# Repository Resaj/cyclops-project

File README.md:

# Cyclops-project

Robot siguelíneas Open Source, diseñado para introducir a nuevos constructores en la robótica de competición. Se compone de dos PCBs: la del chasis autosoportado con la electrónica principal; y la de sensores, que es intercambiable para poder adaptarlo a diferentes pruebas de seguimiento de línea. Incorpora extras de sensores de distancia, cámara y bluetooth, para poder participar en otras pruebas como carreras y laberinto, además de experimentar nuevos métodos de seguimiento de línea o degradado.

El chasis del robot incorpora:
- Arduino nano
- Batería Lipo 2S
- Pulsadores de selección de menú
- Leds indicadores
- Driver de motores TB6612FNG
- Micromotores 10:1 HP 6V con reductora metálica y encoders en cuadratura
- Ruedas de 32mm de diámetro
- Sensor frontal de distancia de 80cm para detección de oponentes (necesario para carreras)
- Sensores laterales de distancia de 35cm para detección de oponentes (necesario para carreras)
- Cámara de 1x128 píxeles para seguimiento de línea y detección de oponentes
- Expansor I2C para poder soportar todos los periféricos incorporados

La PCB de sensores es intercambiable e incorpora:
- Sensores CNY70 para seguimiento de línea (6 para velocista; 8 para rastreador)
- Multiplexor para los sensores de línea

## Manuales y guías del proyecto

Disponibles en la carpeta [manuals](https://github.com/Resaj/cyclops-project/tree/master/manuals):
- [Tutorial 1](https://github.com/Resaj/cyclops-project/blob/master/manuals/Tutorial%201%20-%20Bater%C3%ADas%20Lipo.pdf) - Baterías Lipo
- [Tutorial 2](https://github.com/Resaj/cyclops-project/blob/master/manuals/Tutorial%202%20-%20Impresi%C3%B3n%20de%20las%20piezas%20del%20robot.pdf) - Impresión de las piezas del robot
- [Tutorial 3](https://github.com/Resaj/cyclops-project/blob/master/manuals/Tutorial%203%20-%20Montaje%20del%20robot.pdf) - Montaje del robot
- [Tutorial 4](https://github.com/Resaj/cyclops-project/blob/master/manuals/Tutorial%204%20-%20Configuraci%C3%B3n%20del%20bluetooth%20HC-05.pdf) - Configuración del Bluetooth HC-05
- [Tutorial 5](https://github.com/Resaj/cyclops-project/blob/master/manuals/Tutorial%205%20-%20Primeras%20pruebas.pdf) - Primeras pruebas

A medida que el proyecto vaya avanzando se añadirán más tutoriales para completar la información y facilitar el montaje y la programación del robot.

## Retos planteados para el usuario

Cyclops es un proyecto base para cualquier persona que quiera adentrarse en el mundo de la robótica a través de las competiciones. Por un lado se proporciona una base para el aprendizaje y para facilitar la participación; por otro, se plantean una serie de retos e ideas que servirán a los usuarios para afrontar el desarrollo de un proyecto de robótica y profundizar experimentando con las mejoras:

* General:
  * Mejoras de comunicación por bluetooth con logs de telemetría
*  Rastreador:
  * [Reconocimiento de marcas de giro y selección del camino correcto en las bifurcaciones](https://www.youtube.com/watch?v=3Fi3WpjZuA0)
* Velocistas:
  * Reconocimiento de la [pista](https://github.com/Resaj/basic-circuit-maker) con encoders para acelerar en las rectas y frenar antes de las curvas
  * Adaptación del PID de seguimiento de línea para competir sobre [pistas de degradado](https://github.com/Resaj/circuit-maker)
* Carreras:
  * Detección de oponentes con los sensores de distancia para cambiar de carril y efectuar adelantamientos
  * Implementación de un PID para seguir a un oponente en carreras cuando no se pueda cambiar de carril para adelantar
  * Reconocimiento y seguimiento de líneas y degradados con cámara
* Laberinto:
  * Adaptación del algoritmo de laberinto para seguir la pared derecha en vez de la izquierda
  * Guiarse con los dos sensores laterales y con los encoders para ir siempre centrado en las casillas del laberinto
  * Memorizar las casillas del laberinto en el primer intento para que el robot sea capaz de resolverlo al segundo intento tomando el camino más corto

## Preguntas frecuentes

Puedes encontrar un listado de las preguntas frecuentes con sus respectivas respuestas en la [wiki del proyecto](https://github.com/Resaj/cyclops-project/wiki/FAQ).

## Autor

[Rubén Espino San José](https://github.com/Resaj)

## Agradecimientos y aportaciones

- A Alex @TCRobotics de BricoLabs, por su [tutorial para adaptar el driver CH340G de la Arduino Nano para MAC OS](https://bricolabs.cc/wiki/guias/mac_os_y_ch340)
- A [José Luis Villarejo](https://github.com/movilujo), por los [diseños de las PCBs de Cyclops en FreeCAD](https://github.com/Resaj/cyclops-project/tree/master/hw/FreeCAD/PCBs)
- A [Juan Alberto Babío](https://github.com/jbabio), por la adaptación del [soporte regulable para la cámara](https://github.com/Resaj/cyclops-project/blob/master/hw/FreeCAD/Soporte_inclinable_camara_Aliexpress.stl)
- A Óscar de BricoGeek, por sus streaming ([1](https://www.youtube.com/watch?v=NNreAwnH6MY) y [2](https://www.youtube.com/watch?v=S61M1Ss7pH4)) del montaje de Cyclops-Project
- A [Álex](https://github.com/robotaleh) y [Manuel](https://github.com/20leunam), de [OPRobots](https://github.com/OPRobots), por su [App para calibrar y controlar el robot mediante el bluetooth del móvil](https://github.com/Resaj/cyclops-project/tree/master/fw/PID_seguimiento_linea/PID_seguimiento_linea_PIDfromBT)
- A [Javier Martín](https://github.com/jamarju), por su [adaptación del bootloader de la Arduino para la carga de programas por bluetooth](https://github.com/jamarju/hexloader-avr)

## Licencia

Todos estos productos están liberados mediante [Creative Commons Attribution-ShareAlike 4.0 International License](http://creativecommons.org/licenses/by-sa/4.0/).

_All these products are released under [Creative Commons Attribution-ShareAlike 4.0 International License](http://creativecommons.org/licenses/by-sa/4.0/)._

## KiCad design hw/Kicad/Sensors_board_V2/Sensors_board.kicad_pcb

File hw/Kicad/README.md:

Las huellas de componentes empleadas en el diseño e incluídas en las subcarpetas .pretty pertenecen al repositorio [kicad-footprints](https://github.com/KiCad/kicad-footprints).
Igualmente, los ficheros 3D empleados en el diseño e incluidos en las subcarpetas .3dshapes pertenecen al repositorio [kicad-packages3D](https://github.com/KiCad/kicad-packages3D).

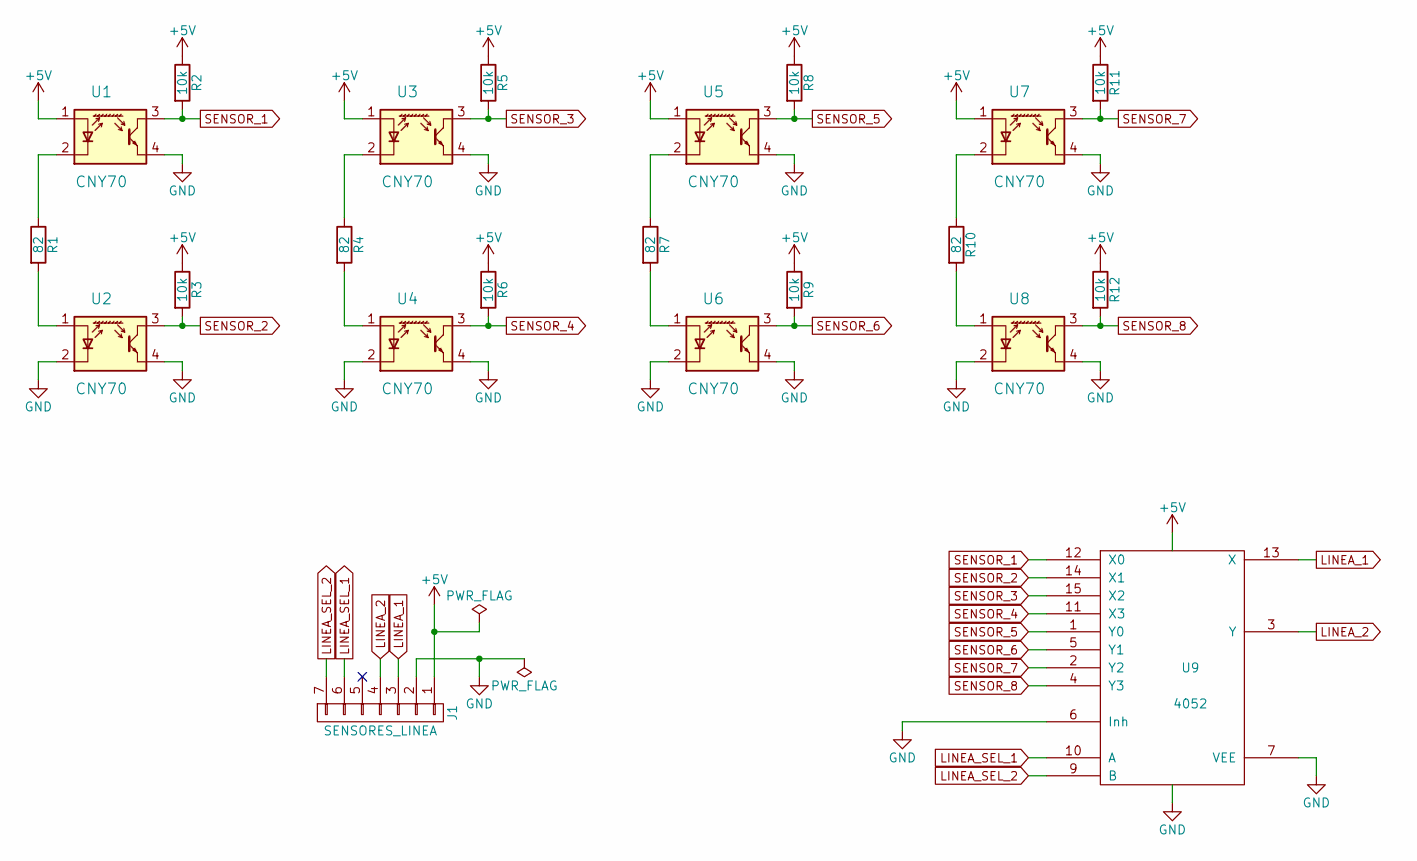
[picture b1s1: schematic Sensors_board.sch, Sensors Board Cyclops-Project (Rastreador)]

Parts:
J1: SENSORES_LINEA; PinHeader_1x07_P2.54mm_Horizontal
R1, R4, R7, R10: 82; R_Axial_DIN0207_L6.3mm_D2.5mm_P10.16mm_Horizontal
R2, R3, R5, R6, R8, R9, R11, R12: 10k; R_Axial_DIN0207_L6.3mm_D2.5mm_P10.16mm_Horizontal
U1, U2, U3, U4, U5, U6, U7, U8: CNY70; Vishay_CNY70
U9: 4052; DIP-16_W7.62mm_Socket_LongPads

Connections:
+5V: J1.1, R2.1, R3.1, R5.1, R6.1, R8.1, R9.1, R11.1, R12.1, U1.1 (A), U3.1 (A), U5.1 (A), U7.1 (A), U9.16 (VDD)
GND: J1.2, U1.4 (E), U2.2 (K), U2.4 (E), U3.4 (E), U4.2 (K), U4.4 (E), U5.4 (E), U6.2 (K), U6.4 (E), U7.4 (E), U8.2 (K), U8.4 (E), U9.6 (Inh), U9.7 (VEE), U9.8 (VSS)
LINEA_1: J1.3, U9.13 (X)
LINEA_2: J1.4, U9.3 (Y)
LINEA_SEL_1: J1.6, U9.10 (A)
LINEA_SEL_2: J1.7, U9.9 (B)
unnamed: R1.1, U1.2 (K)
unnamed: R1.2, U2.1 (A)
unnamed: R4.1, U3.2 (K)
unnamed: R4.2, U4.1 (A)
unnamed: R7.1, U5.2 (K)
unnamed: R7.2, U6.1 (A)
unnamed: R10.1, U7.2 (K)
unnamed: R10.2, U8.1 (A)
SENSOR_1: R2.2, U1.3 (C), U9.12 (X0)
SENSOR_2: R3.2, U2.3 (C), U9.14 (X1)
SENSOR_3: R5.2, U3.3 (C), U9.15 (X2)
SENSOR_4: R6.2, U4.3 (C), U9.11 (X3)
SENSOR_5: R8.2, U5.3 (C), U9.1 (Y0)
SENSOR_6: R9.2, U6.3 (C), U9.5 (Y1)
SENSOR_7: R11.2, U7.3 (C), U9.2 (Y2)
SENSOR_8: R12.2, U8.3 (C), U9.4 (Y3)

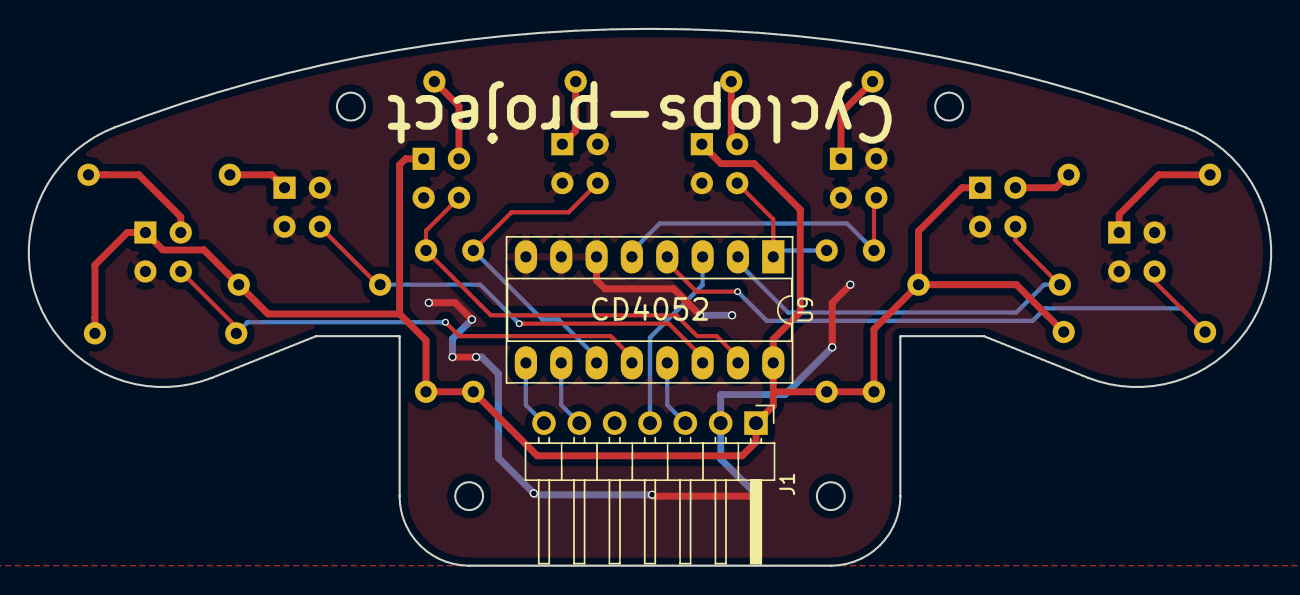
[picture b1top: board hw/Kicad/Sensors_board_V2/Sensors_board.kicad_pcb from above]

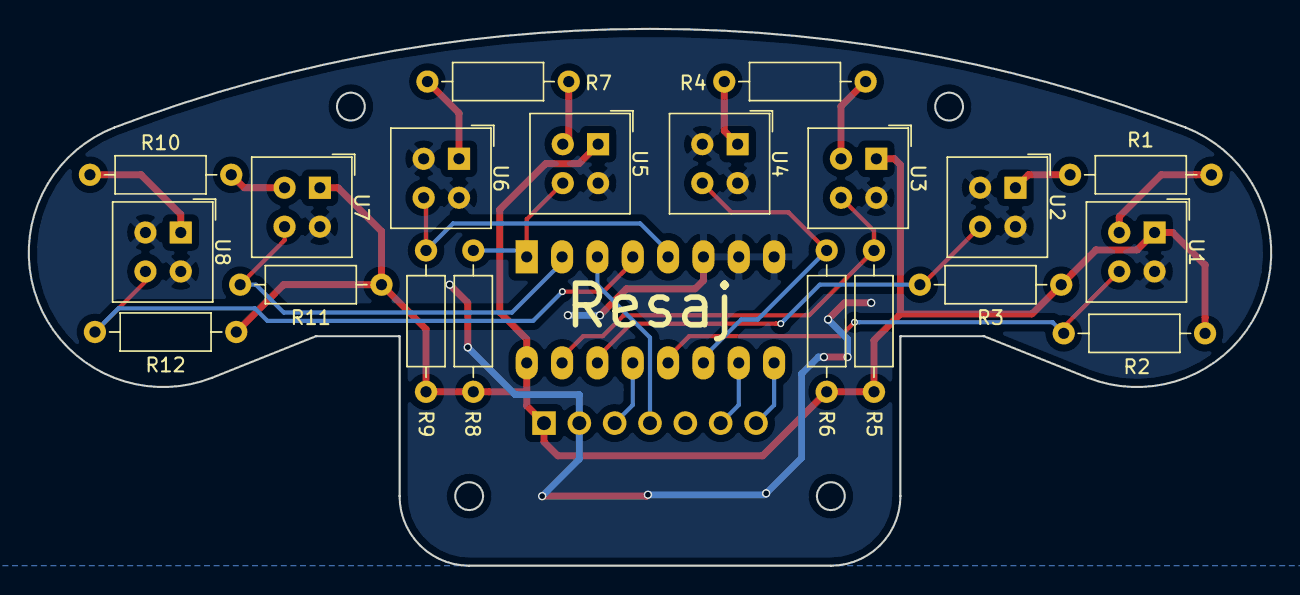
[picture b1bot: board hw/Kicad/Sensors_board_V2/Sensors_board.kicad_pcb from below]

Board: 2 copper layers, 89.3 x 38.6 mm, 22 parts (20 on the bottom side), 22 nets.

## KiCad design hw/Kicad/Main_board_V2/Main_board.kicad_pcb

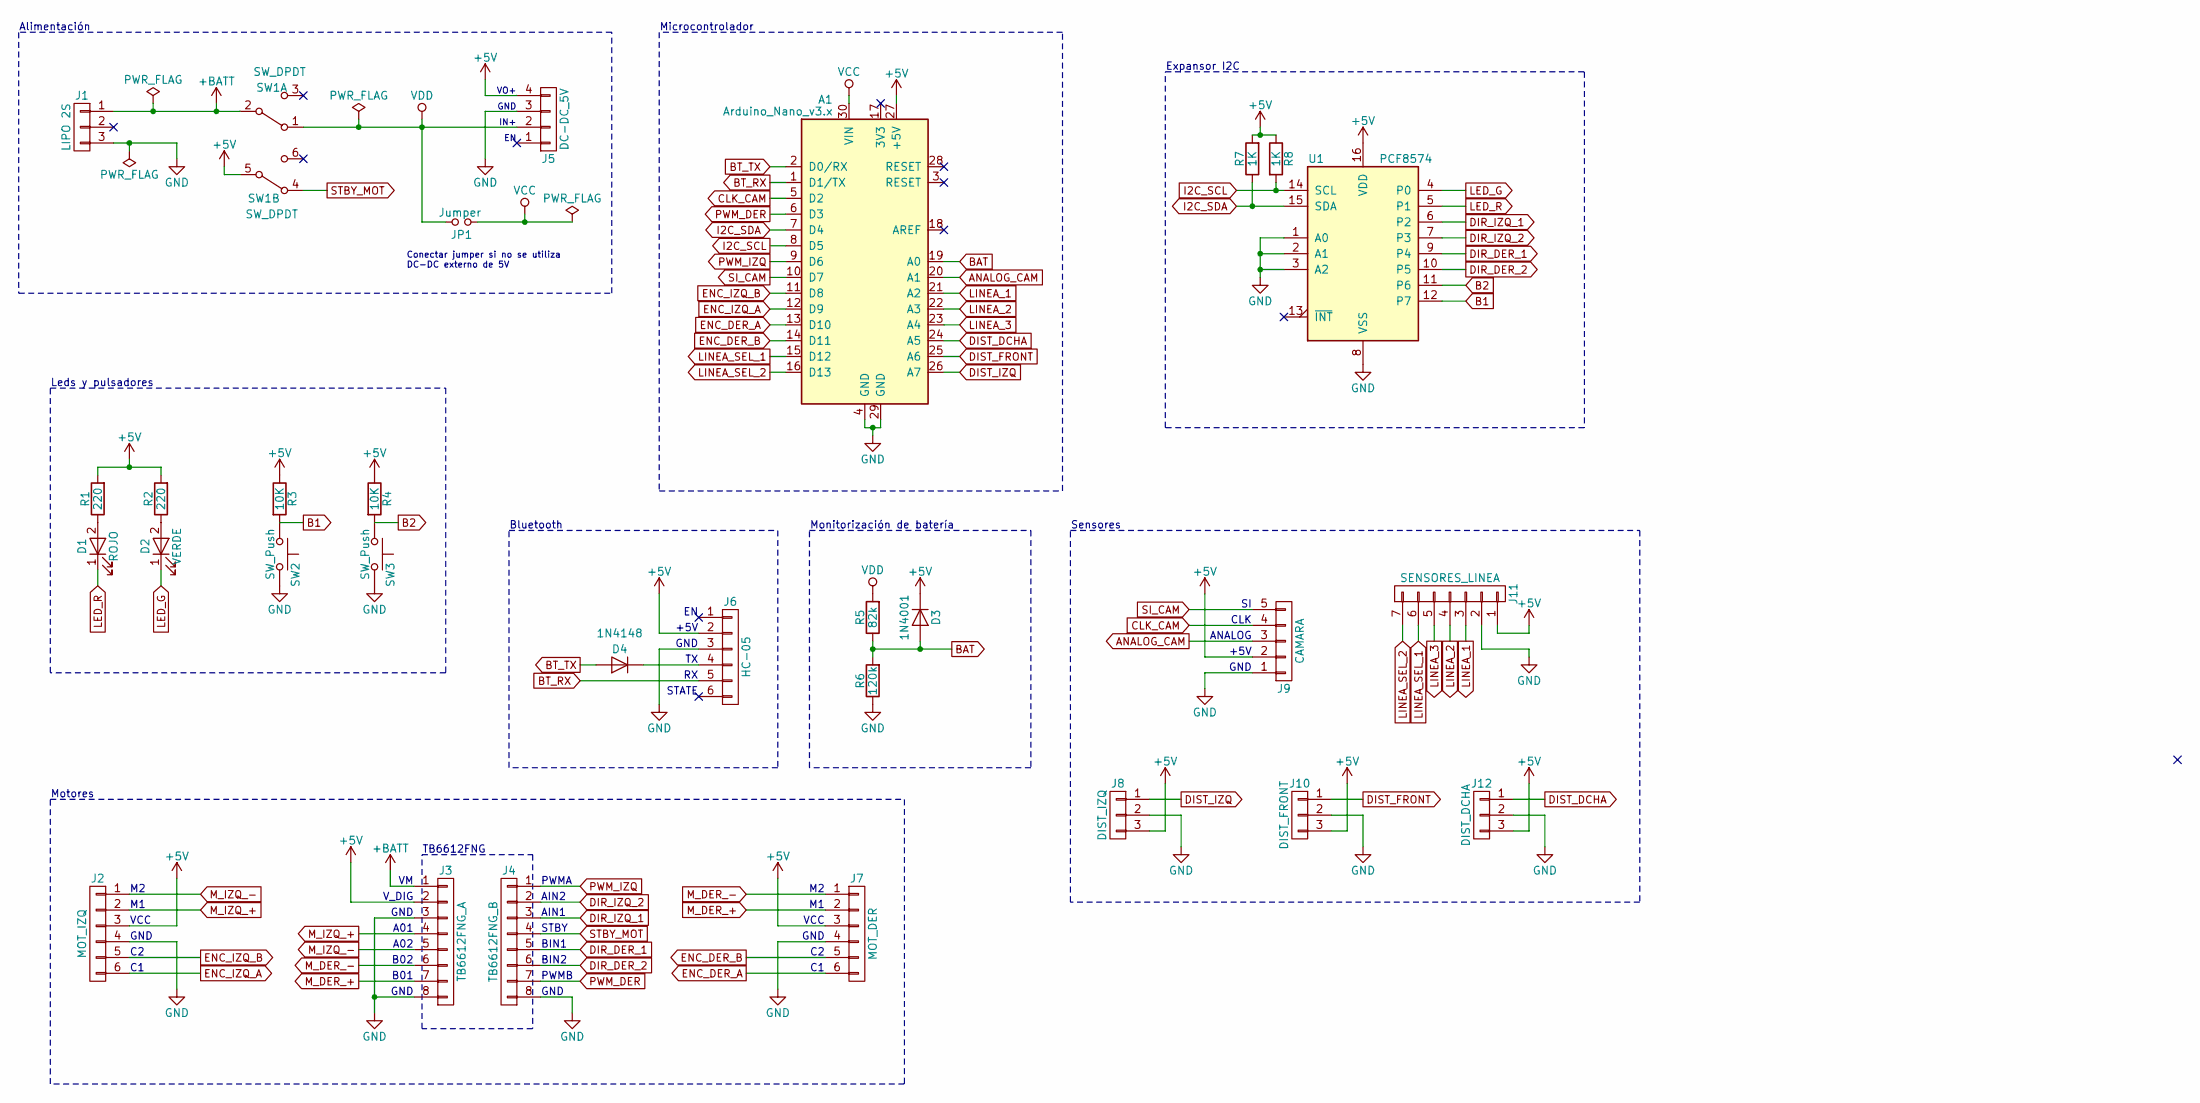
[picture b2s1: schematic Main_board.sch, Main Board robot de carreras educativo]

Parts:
A1: Arduino_Nano_v3.x; Arduino_Nano
D1: ROJO; LED_D3.0mm
D2: VERDE; LED_D3.0mm
D3: 1N4001; D_A-405_P10.16mm_Horizontal
D4: 1N4148; D_A-405_P10.16mm_Horizontal
J1: LIPO 2S; JST_XH_B03B-XH-A_1x03_P2.50mm_Vertical
J2: MOT_IZQ; PinHeader_1x06_P2.00mm_Vertical
J3: TB6612FNG_A; PinSocket_1x08_P2.54mm_Vertical
J4: TB6612FNG_B; PinSocket_1x08_P2.54mm_Vertical
J5: DC-DC_5V; PinSocket_1x04_P2.54mm_Horizontal
J6: HC-05; PinSocket_1x06_P2.54mm_Vertical
J7: MOT_DER; PinHeader_1x06_P2.00mm_Vertical
J8: DIST_IZQ; PinHeader_1x03_P2.00mm_Vertical
J9: CAMARA; PinHeader_1x05_P2.54mm_Vertical
J10: DIST_FRONT; PinHeader_1x03_P2.00mm_Vertical
J11: SENSORES_LINEA; PinSocket_1x07_P2.54mm_Horizontal
J12: DIST_DCHA; PinHeader_1x03_P2.00mm_Vertical
JP1: Jumper; SolderJumper-2_P1.3mm_Open_Pad1.0x1.5mm
R1, R2: 220; R_Axial_DIN0207_L6.3mm_D2.5mm_P10.16mm_Horizontal
R3, R4: 10K; R_Axial_DIN0207_L6.3mm_D2.5mm_P10.16mm_Horizontal
R5: 82k; R_Axial_DIN0207_L6.3mm_D2.5mm_P10.16mm_Horizontal
R6: 120k; R_Axial_DIN0207_L6.3mm_D2.5mm_P10.16mm_Horizontal
R7, R8: 1K; R_Axial_DIN0207_L6.3mm_D2.5mm_P10.16mm_Horizontal
SW1: SW_DPDT; SW_CuK_JS202011CQN_DPDT_Straight
SW2, SW3: SW_Push; SW_PUSH_6mm
U1: PCF8574; DIP-16_W7.62mm_Socket_LongPads

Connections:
+5V: A1.27 (+5V), D3.1 (K), J2.3, J3.2, J5.4, J6.2, J7.3, J8.3, J9.2, J10.3, J11.1, J12.3, R1.2, R2.2, R3.1, R4.1, R7.2, R8.1, SW1.5 (B), U1.16 (VDD)
+BATT: J1.1, J3.1, SW1.2 (B)
ANALOG_CAM: A1.20 (A1), J9.3
B1: R3.2, SW2.1, U1.12 (P7)
B2: R4.2, SW3.1, U1.11 (P6)
BAT: A1.19 (A0), D3.2 (A), R5.1, R6.2
BT_RX: A1.1 (D1/TX), J6.5
BT_TX: A1.2 (D0/RX), D4.2 (A)
CLK_CAM: A1.5 (D2), J9.4
DIR_DER_1: J4.5, U1.9 (P4)
DIR_DER_2: J4.6, U1.10 (P5)
DIR_IZQ_1: J4.3, U1.6 (P2)
DIR_IZQ_2: J4.2, U1.7 (P3)
DIST_DCHA: A1.24 (A5), J12.1
DIST_FRONT: A1.25 (A6), J10.1
DIST_IZQ: A1.26 (A7), J8.1
ENC_DER_A: A1.13 (D10), J7.6
ENC_DER_B: A1.14 (D11), J7.5
ENC_IZQ_A: A1.12 (D9), J2.6
ENC_IZQ_B: A1.11 (D8), J2.5
GND: A1.4 (GND), A1.29 (GND), J1.3, J2.4, J3.3, J3.8, J4.8, J5.3, J6.3, J7.4, J8.2, J9.1, J10.2, J11.2, J12.2, R6.1, SW2.2, SW3.2, U1.1 (A0), U1.2 (A1), U1.3 (A2), U1.8 (VSS)
I2C_SCL: A1.8 (D5), R8.2, U1.14 (SCL)
I2C_SDA: A1.7 (D4), R7.1, U1.15 (SDA)
LED_G: D2.1 (K), U1.4 (P0)
LED_R: D1.1 (K), U1.5 (P1)
LINEA_1: A1.21 (A2), J11.3
LINEA_2: A1.22 (A3), J11.4
LINEA_3: A1.23 (A4), J11.5
LINEA_SEL_1: A1.15 (D12), J11.6
LINEA_SEL_2: A1.16 (D13), J11.7
M_DER_+: J3.7, J7.2
M_DER_-: J3.6, J7.1
M_IZQ_+: J2.2, J3.4
M_IZQ_-: J2.1, J3.5
unnamed: D1.2 (A), R1.1
unnamed: D2.2 (A), R2.1
unnamed: D4.1 (K), J6.4
PWM_DER: A1.6 (D3), J4.7
PWM_IZQ: A1.9 (D6), J4.1
SI_CAM: A1.10 (D7), J9.5
STBY_MOT: J4.4, SW1.4 (A)
VCC: A1.30 (VIN), JP1.1
VDD: J5.2, JP1.2, R5.2, SW1.1 (A)

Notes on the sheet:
VO+
IN+
GND
Conectar jumper si no se utiliza DC-DC externo de 5V
Alimentación
Microcontrolador
Leds y pulsadores
Monitorización de batería
V_DIG
A01
A02
B02
B01
PWMB
PWMA
AIN2
AIN1
STBY
BIN1
BIN2
VCC
TB6612FNG
Motores
+5V
STATE
Bluetooth
ANALOG
CLK
Sensores
Expansor I2C

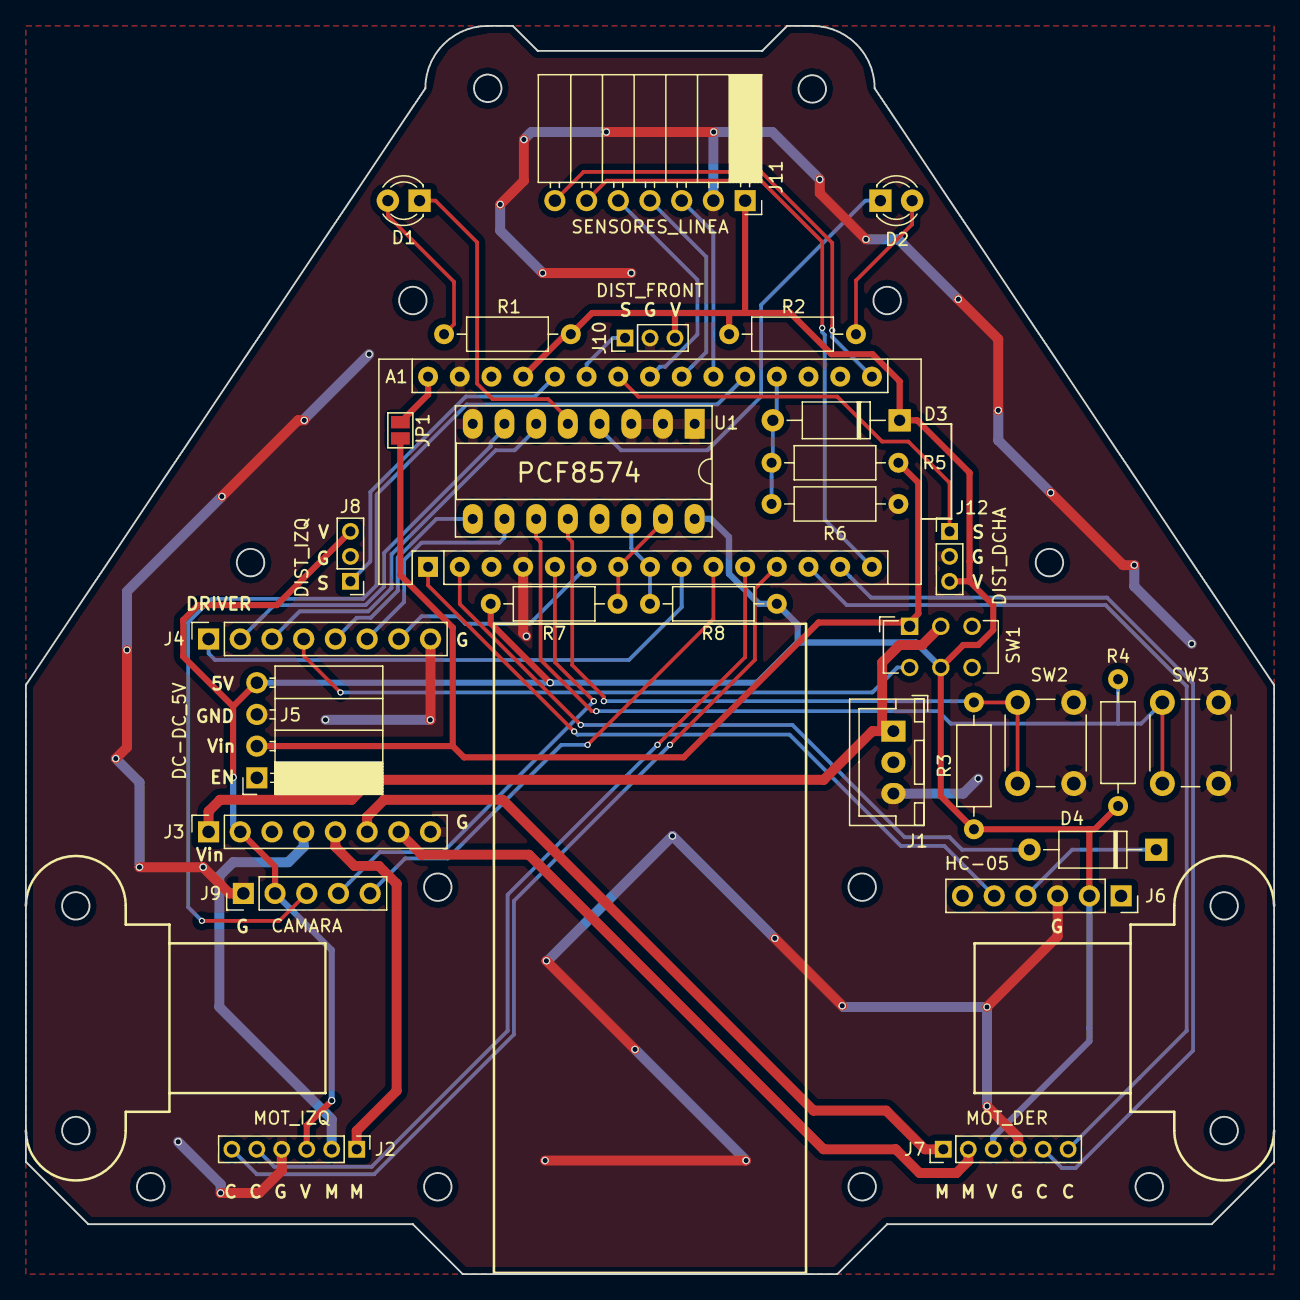
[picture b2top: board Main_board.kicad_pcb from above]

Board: 2 copper layers, 100.0 x 100.0 mm, 30 parts (0 on the bottom side), 43 nets.

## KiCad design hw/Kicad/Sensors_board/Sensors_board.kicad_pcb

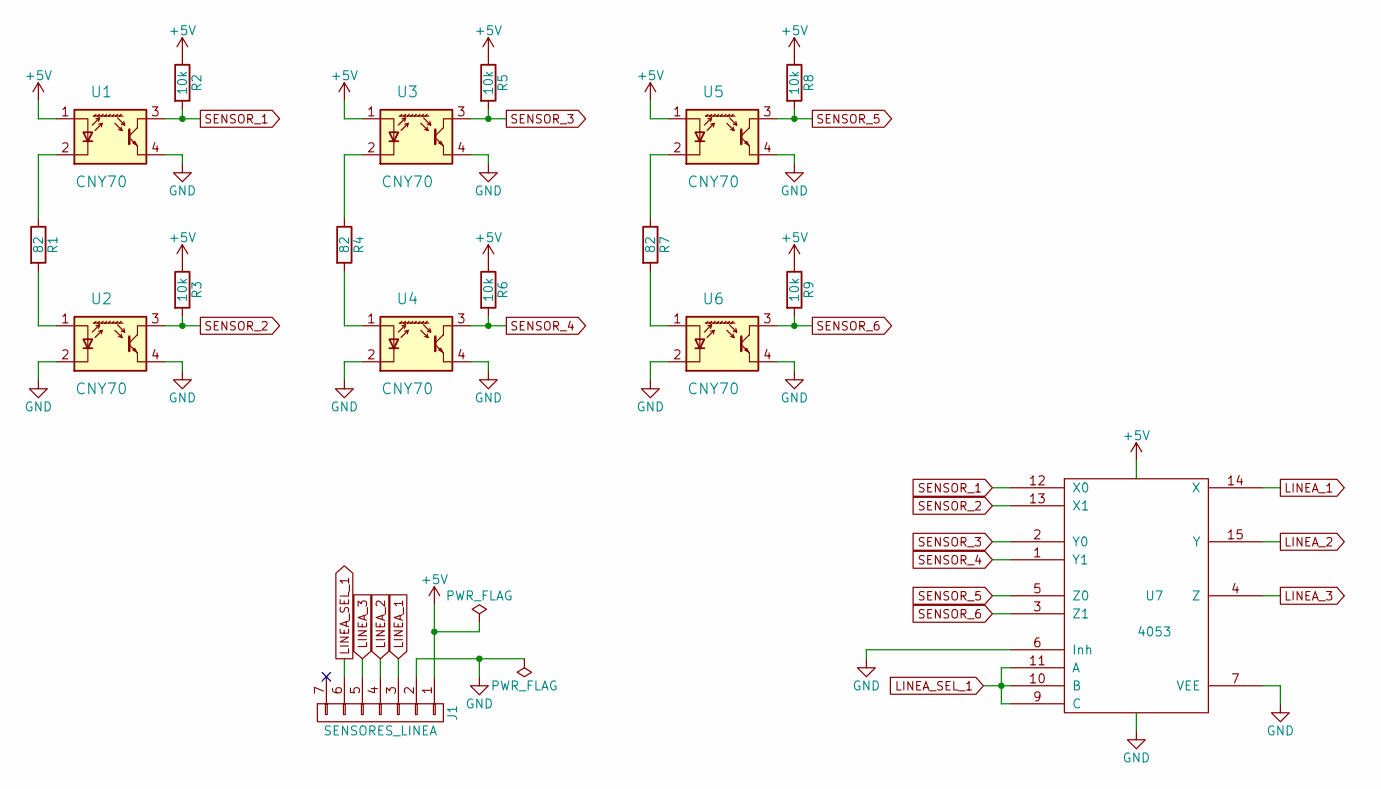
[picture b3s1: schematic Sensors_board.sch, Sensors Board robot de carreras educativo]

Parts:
J1: SENSORES_LINEA; PinHeader_1x07_P2.54mm_Horizontal
R1, R4, R7: 82; R_Axial_DIN0207_L6.3mm_D2.5mm_P10.16mm_Horizontal
R2, R3, R5, R6, R8, R9: 10k; R_Axial_DIN0207_L6.3mm_D2.5mm_P10.16mm_Horizontal
U1, U2, U3, U4, U5, U6: CNY70; Vishay_CNY70
U7: 4053; DIP-16_W7.62mm_Socket_LongPads

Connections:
+5V: J1.1, R2.1, R3.1, R5.1, R6.1, R8.1, R9.1, U1.1 (A), U3.1 (A), U5.1 (A), U7.16 (VDD)
GND: J1.2, U1.4 (E), U2.2 (K), U2.4 (E), U3.4 (E), U4.2 (K), U4.4 (E), U5.4 (E), U6.2 (K), U6.4 (E), U7.6 (Inh), U7.7 (VEE), U7.8 (VSS)
LINEA_1: J1.3, U7.14 (X)
LINEA_2: J1.4, U7.15 (Y)
LINEA_3: J1.5, U7.4 (Z)
LINEA_SEL_1: J1.6, U7.9 (C), U7.10 (B), U7.11 (A)
unnamed: R1.1, U1.2 (K)
unnamed: R1.2, U2.1 (A)
unnamed: R4.1, U3.2 (K)
unnamed: R4.2, U4.1 (A)
unnamed: R7.1, U5.2 (K)
unnamed: R7.2, U6.1 (A)
SENSOR_1: R2.2, U1.3 (C), U7.12 (X0)
SENSOR_2: R3.2, U2.3 (C), U7.13 (X1)
SENSOR_3: R5.2, U3.3 (C), U7.2 (Y0)
SENSOR_4: R6.2, U4.3 (C), U7.1 (Y1)
SENSOR_5: R8.2, U5.3 (C), U7.5 (Z0)
SENSOR_6: R9.2, U6.3 (C), U7.3 (Z1)

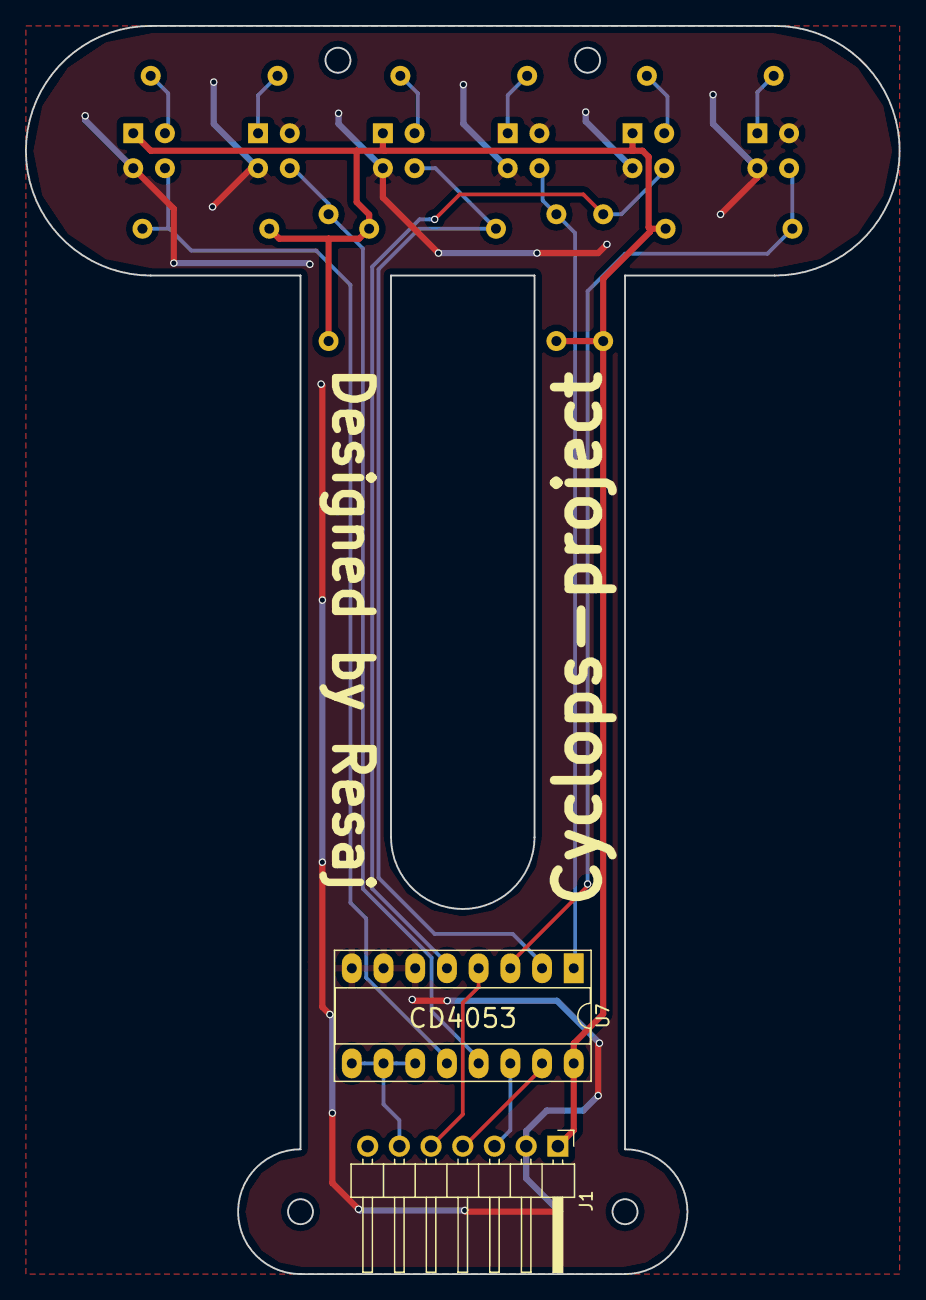
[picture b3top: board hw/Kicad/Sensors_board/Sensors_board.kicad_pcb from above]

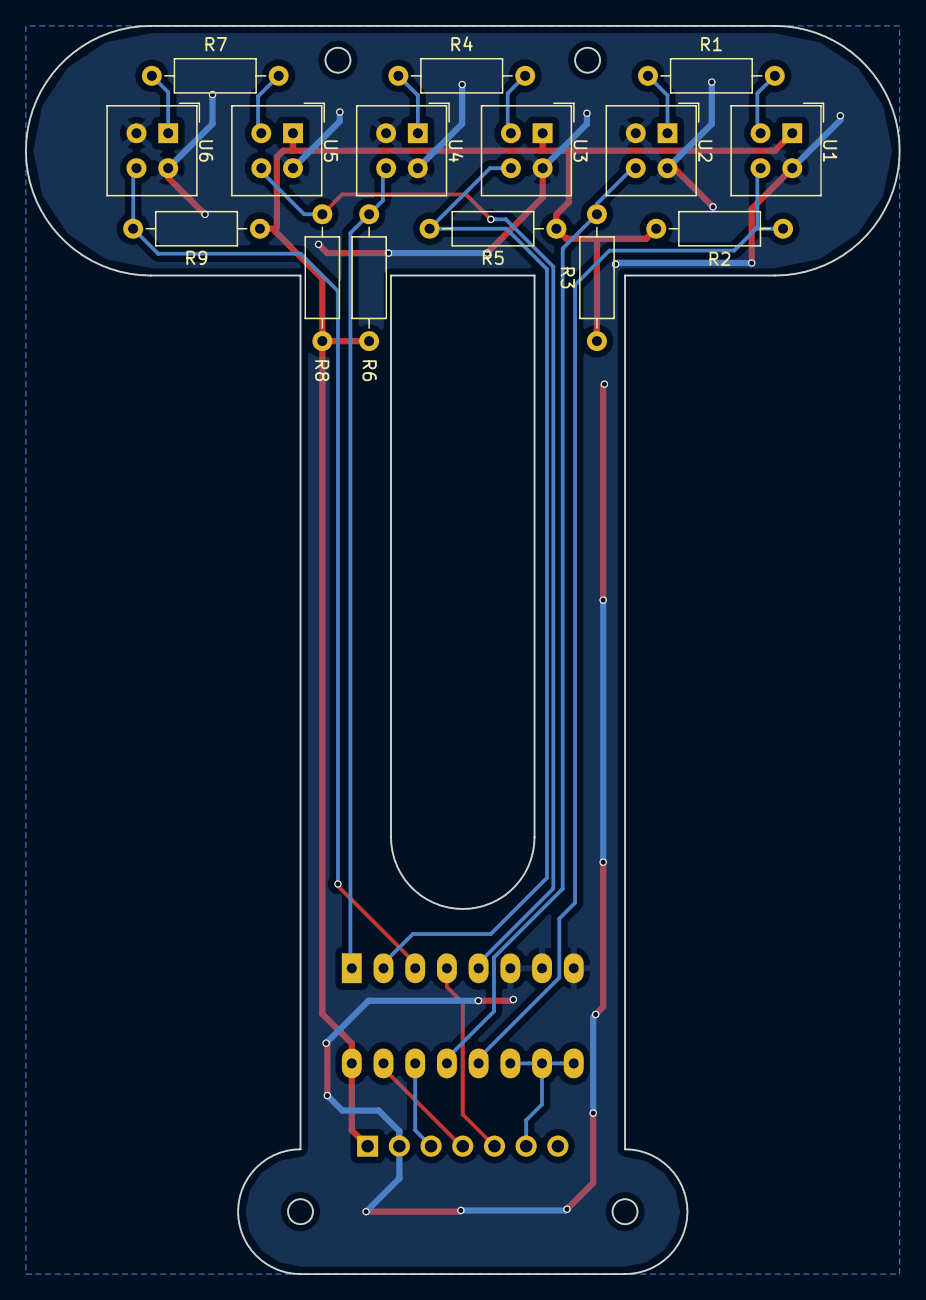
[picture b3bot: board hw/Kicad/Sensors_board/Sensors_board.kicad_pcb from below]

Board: 2 copper layers, 70.0 x 100.0 mm, 17 parts (15 on the bottom side), 18 nets.

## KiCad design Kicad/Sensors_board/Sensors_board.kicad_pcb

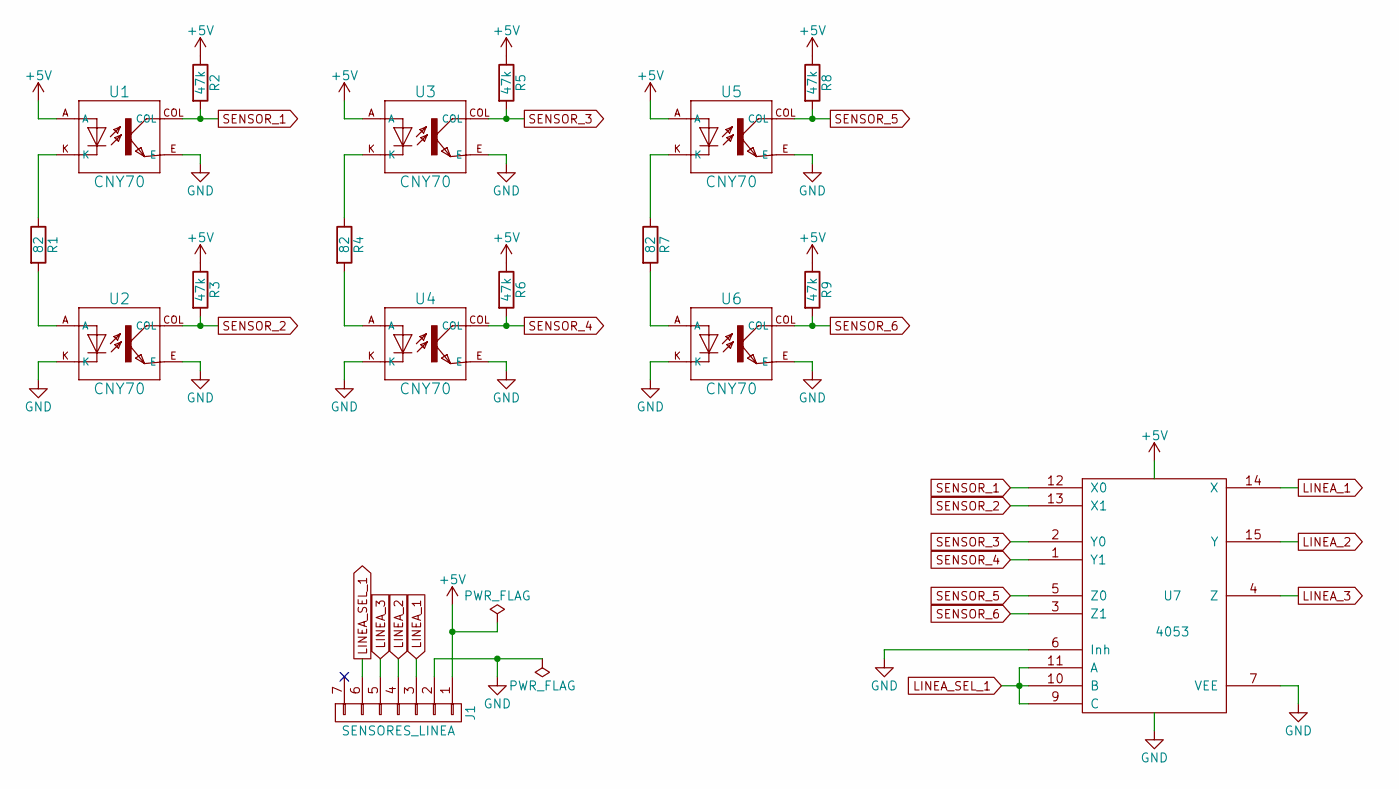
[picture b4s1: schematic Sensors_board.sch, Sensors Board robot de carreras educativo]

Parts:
J1: SENSORES_LINEA; Pin_Header_Angled_1x07_Pitch2.54mm
R1, R4, R7: 82; R_Axial_DIN0207_L6.3mm_D2.5mm_P10.16mm_Horizontal
R2, R3, R5, R6, R8, R9: 47k; R_Axial_DIN0207_L6.3mm_D2.5mm_P10.16mm_Horizontal
U1, U2, U3, U4, U5, U6: CNY70
U7: 4053; DIP-16_W7.62mm_LongPads

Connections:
+5V: J1.1, R2.1, R3.1, R5.1, R6.1, R8.1, R9.1, U1.A, U3.A, U5.A, U7.16 (VDD)
GND: J1.2, U1.E, U2.E, U2.K, U3.E, U4.E, U4.K, U5.E, U6.E, U6.K, U7.6 (Inh), U7.7 (VEE), U7.8 (VSS)
LINEA_1: J1.3, U7.14 (X)
LINEA_2: J1.4, U7.15 (Y)
LINEA_3: J1.5, U7.4 (Z)
LINEA_SEL_1: J1.6, U7.9 (C), U7.10 (B), U7.11 (A)
unnamed: R1.1, U1.K
unnamed: R1.2, U2.A
unnamed: R4.1, U3.K
unnamed: R4.2, U4.A
unnamed: R7.1, U5.K
unnamed: R7.2, U6.A
SENSOR_1: R2.2, U1.COL, U7.12 (X0)
SENSOR_2: R3.2, U2.COL, U7.13 (X1)
SENSOR_3: R5.2, U3.COL, U7.2 (Y0)
SENSOR_4: R6.2, U4.COL, U7.1 (Y1)
SENSOR_5: R8.2, U5.COL, U7.5 (Z0)
SENSOR_6: R9.2, U6.COL, U7.3 (Z1)

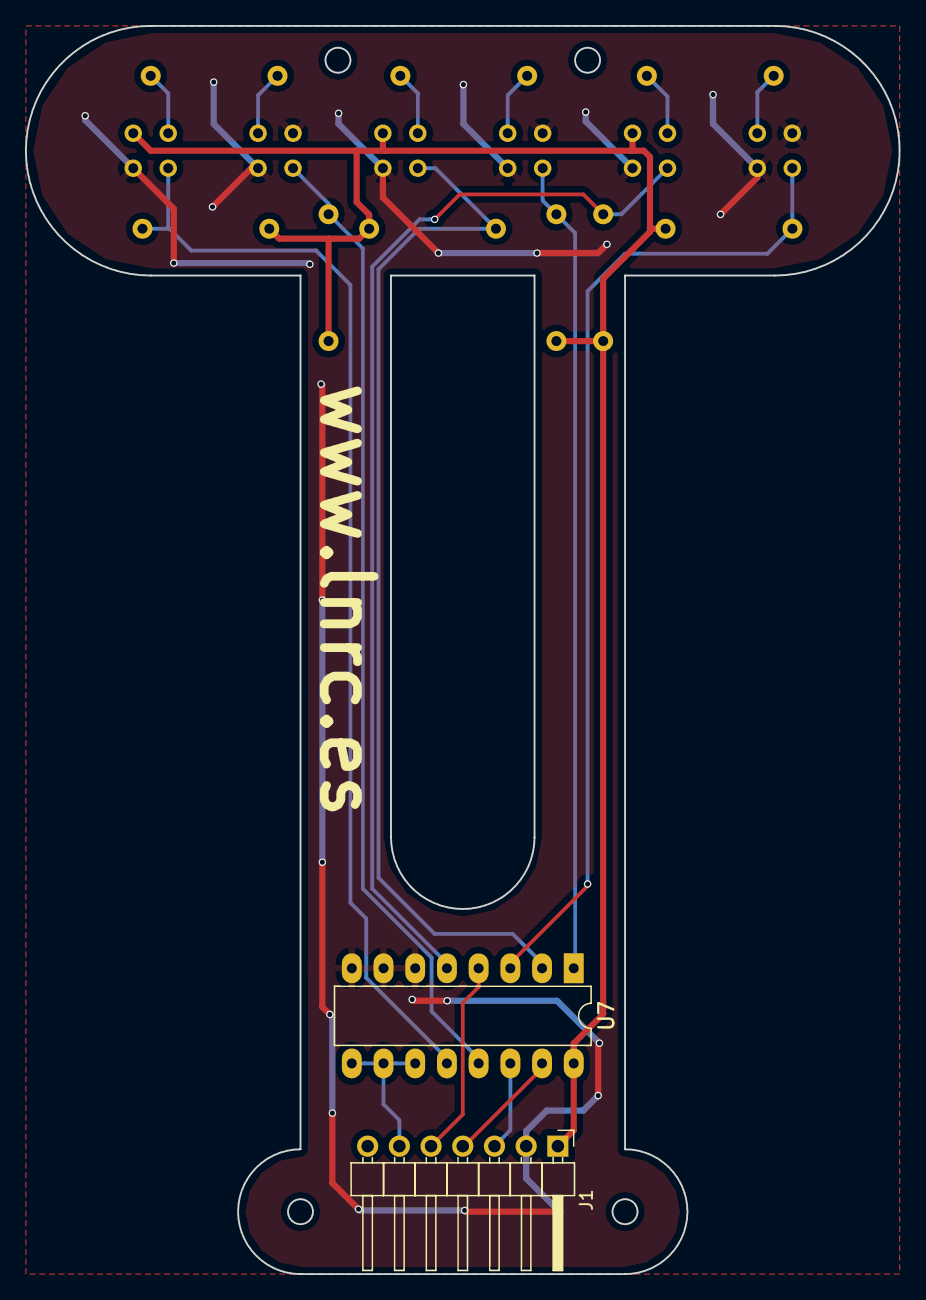
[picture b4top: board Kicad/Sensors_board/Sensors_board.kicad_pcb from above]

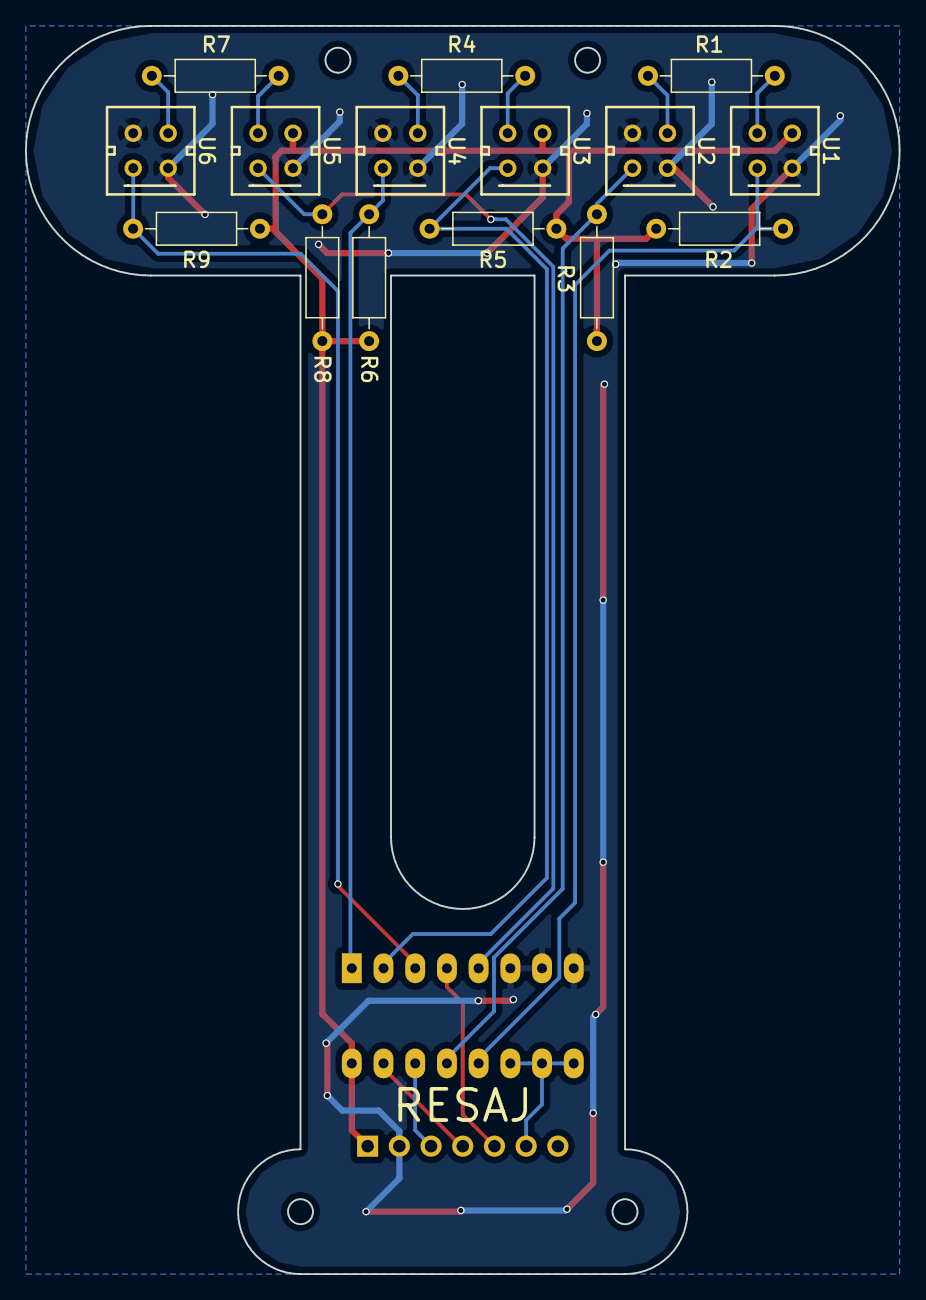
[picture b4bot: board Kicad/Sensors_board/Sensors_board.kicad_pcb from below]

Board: 2 copper layers, 70.0 x 100.0 mm, 17 parts (15 on the bottom side), 18 nets.

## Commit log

2017-07-04 Kicad files added
2017-07-04 Pin selection file added
2017-07-19 Motor driver position adjusted
2017-07-28 BOMs and PDF schematic added
2017-07-29 BOM added
2017-07-29 Some 3D designs added
2017-07-30 Screen modified
2017-07-30 Sensor holder added
2017-07-30 BOM modified
2017-07-30 Sensors holder modified
2017-07-30 Camera holder added
2017-07-31 Batty connector modified in BOM
2017-07-31 Camera holder modified
2017-07-31 Resistors modified
2017-08-01 DC-DC enable modified
2017-08-01 Wheels link modified
2017-08-02 Right angle male pin header link modified in BOM
2017-08-02 Link of lipo charger modified
2017-08-03 Wheels modified in BOM
2017-08-03 Some pictures added
2017-08-03 Readme modified
2017-08-10 fw and hw folders added
2017-08-13 Leds connections modified and I2C resistors added
2017-08-13 Firmware test added
2017-08-23 Camera test added
2017-08-24 Camera sample period programmed
2017-08-24 Encoders tested
2017-09-05 Gerbers actualized and motors connector changed
2017-09-23 I2C resistor values changed
2017-09-24 Lipo manual added
2017-10-04 Bluetooth configuration added
2017-10-06 PDF bluetooth manual added
2017-10-06 PID test added
2017-10-06 Readmes of programs added
2017-10-11 3D printing parts tutorial added
2017-10-12 3D printing parts tutorial modified
2017-10-20 Assembly manual added
2017-10-23 Address changed for different types of I2C expander
2017-10-25 Setup bug fixed
2017-10-25 Input modes specified for different encoders
2017-10-25 Another option for motors added
2017-10-25 Manuals arranged
2017-10-30 First tests manual added
2017-10-30 Manual 5 modified
2017-10-31 Manual 5 updated
2017-10-31 Blink as first test
2017-11-03 Modified some details of manual 3
2017-11-05 Sensors calibration added and PID adjusted
2017-11-05 Camera added in PID test
2017-11-05 Details of PID test changed
2017-11-05 Sheet for calculation of proporcional factor of PID added
2017-11-09 Changed some variables
2017-11-18 Link of BricoLabs' Guide for CH340G and MAC added
2017-11-18 Some references changed
2017-11-18 Some details remarked
2017-12-01 PCB silk modified
2017-12-04 Pantalla trasera ampliada
2017-12-30 Battery monitor code modified
2018-01-19 Create xx
2018-01-19 Assembly manual modified
2018-01-20 Test readme modified
2018-01-20 Created readme fw
2018-01-20 BOM modified
    BOM moved to hw folder
2018-01-20 PDF HC-05 config modified
2018-01-20 Main_board version specified
2018-01-20 Main_board V2 generated
    Diode added on Bluetooth Tx connection
2018-01-20 Documentation modified for Main_board_V2
2018-01-21 Histeresis en led de bateria baja
2018-01-21 First test manual modified
2018-01-21 SoftWire library added
2018-01-30 Modificadas rutas de librerias de Kicad
2018-01-30 Cambiado valor del diodo D4
2018-01-30 Cambiado diodo D4 en tutorial y BOM
2018-02-15 Añadido soporte inclinable para camara Aliexpress.
    Se añade soporte con inclinación variable para la cámara de Aliexpress, Se requieren dos tornillos M2x8 adicionales.
2018-02-15 Tutorial 2 modified
    jbabio's camera holder added
2018-03-07 Corregida lectura de bateria
2018-07-12 Files updated with icons
2018-07-12 Readme modify
2018-07-12 PCBs silkscreen updated
2018-07-30 Bricogeek streaming references added
2018-08-07 PCBs adapted with Kicad libraries models
2018-08-07 3D model for Arduino Nano socket added
2018-08-07 PCBs FreeCAD models created with Kicad StepUp
2018-08-18 Velocista image changed
2018-08-19 Silkscreen fixed
2018-10-02 Añade control a través de la APP PIDfromBT
    Implementado control del PID del siguelineas a traves de la APP movil PIDfromBT para una experiencia de uso ALUCINANTE!!!
    Librería -> https://github.com/robotaleh/PIDfromBTlib
    APP -> https://github.com/robotaleh/PIDfromBT
2018-10-02 Añade librería PIDfromBT
2018-10-04 Assembly guide details added
2018-10-25 Modified some details
2018-11-12 Firmware sorteo Cyclops 100
2018-11-22 Modified some details of bluetooth manual
2018-11-22 Modified default speed of example program
2018-11-22 Added some details about motors
2018-11-23 Modified some details of manuals
2018-11-24 Moved PIDfromBT program and modified readme files
2018-11-24 Readme files modified
2018-11-25 Added motor option to manual
2018-11-25 3D model of basic assembly added
2018-11-25 Added encoder discs to 3D model
2018-11-29 Motor test modified for new wires
2018-12-04 Added charge by bluetooth references
2018-12-13 Bug fixed
2018-12-18 Wiki images added
2018-12-21 CNY70 schematic image added
2018-12-21 CNY70 images added
2018-12-22 Wiki bluetooth image added
2018-12-22 Wiki UART image added
2018-12-22 Wifi UART image modified
2018-12-22 FAQ reference added to Readme
2018-12-23 Wiki supply image added
2018-12-24 Wiki GP2Y image added
2018-12-24 Wifi GP2Y0A21 function image added
2018-12-28 Wiki Arduino Uno connector image added
2018-12-28 Wiki bluetooth UART image modified
2019-01-04 Wiki motor connection images added
2019-03-03 Some details changed
2019-03-03 Sensors_board_V2 Schematic, pdf and bom added
2019-03-04 PCB Sensors_board_V2 designed
2019-03-04 Ground plane modified
2019-03-04 Sensors_board_V2 3D files added
2019-03-04 Sensors_board_V2 gerbers added
2019-03-05 Included CD4052 socket
2019-03-05 Robot assembly with Sensors_board_V2 added
2019-03-05 Assembly images with Sensors_board_V2 added
2019-03-06 Sensors_board_V2 added to test FW
2019-03-06 PID proportional calculation for 8 sensors added
2019-03-06 PID readme modified
2019-03-06 PID fw modified for Sensors_board_V2
2019-03-06 PIDfromBT fw modified for Sensors_board_V2
2019-03-06 Modified BOM for added sensors_board_V2
2019-03-06 Sensors boards configuration specified in tutorial 5
2019-03-06 Gerbers modified
2019-03-07 Changed BOM details
2019-03-08 Challenges added
2019-03-08 Added links for challenges
2019-03-08 Added new challenge
2019-03-08 Readme image changed
2019-03-08 Tutorial references added in Readme
2019-03-31 Manual 3 adapted for last changes
2019-04-01 Bug fixed in line sensors test
2019-04-01 Rastreator image added
2019-04-09 Sensors_board_V2 references added for manual 3
2019-04-18 Modificado readme fw
2019-04-20 Labyrinth code added
2019-04-20 Front distance sensor height fixed to avoid multiplexer
2019-05-03 FW test fixed
2019-09-09 Modificados los gerbers de la PCB de sensores para rastreador
2020-03-12 Wiki images added with math formules
2020-03-21 Wiki graphs added
2022-04-22 Actualizados detalles de montaje de DC-DC y CNY70
2022-07-27 manuals. Mejoras de descripciones en el manual 5
